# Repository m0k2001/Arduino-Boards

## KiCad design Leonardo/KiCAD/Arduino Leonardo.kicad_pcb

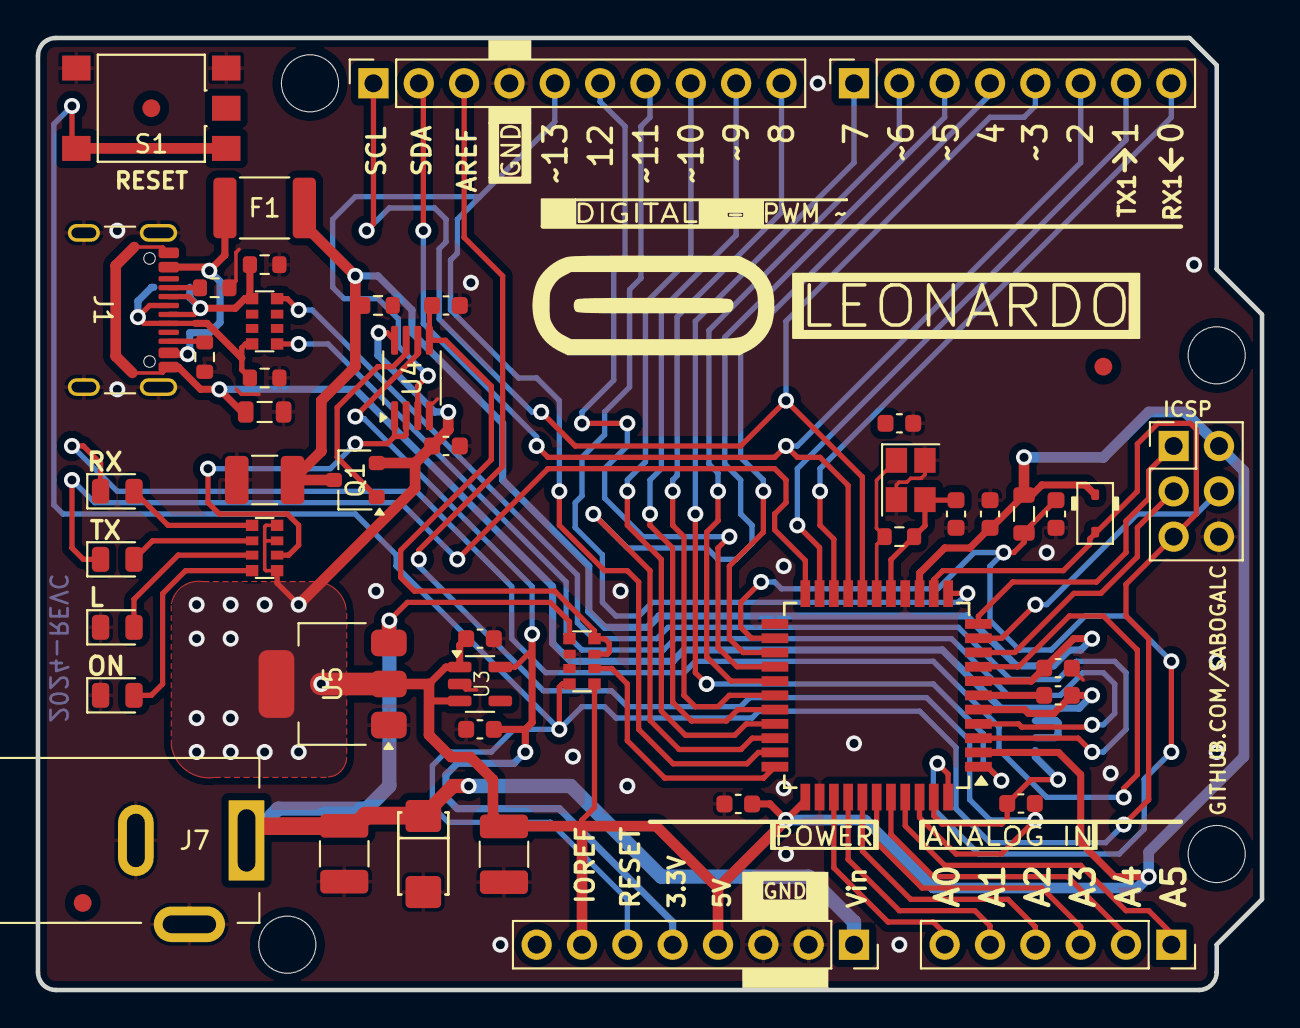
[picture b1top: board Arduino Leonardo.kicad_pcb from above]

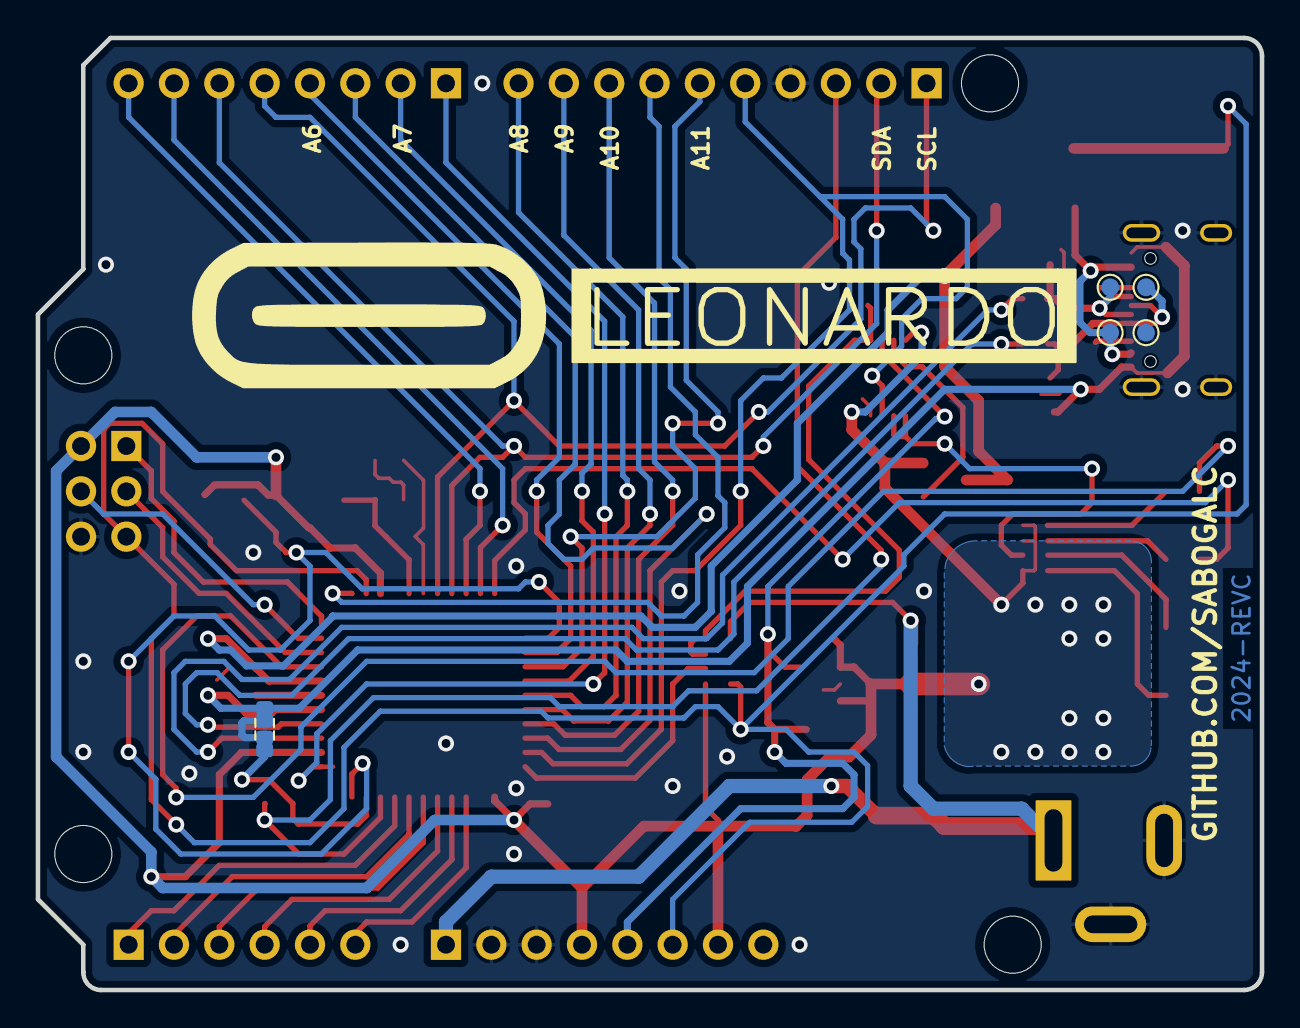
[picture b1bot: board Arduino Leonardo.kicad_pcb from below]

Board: 2 copper layers, 68.6 x 53.3 mm, 56 parts (6 on the bottom side), 53 nets.

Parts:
C1, C2, C6, C9, C13, C22: 100n; C_0603_1608Metric
C3, C4: 22p; C_0603_1608Metric
C5, C7, C11, C14: 1u; C_0603_1608Metric
C8, C10, C12: 10u; C_1210_3225Metric_Pad1.33x2.70mm_HandSolder
D1: M7; D_DO-214AC(SMA)
D2: 1N4148WS; D_SOD-323
D3, D5, D6: YELLOW; LED_0805_2012Metric
D4: GREEN; LED_0805_2012Metric
F1: MF-MSMF050-2; Fuse_1812_4532Metric_Pad1.30x3.40mm_HandSolder
FB1, FB2: 1kΩ@100MHz; L_0805_2012Metric
FID1, FID2, FID3: Fiducial; Fiducial_1mm_Mask2mm
J1: USB_C_Receptacle_USB2.0_16P; USB_C_Receptacle_GCT_USB4105-xx-A_16P_TopMnt_Horizontal
J2: PPTC101LFBN-RC; PinSocket_1x10_P2.54mm_Vertical
J3, J4: PPTC081LFBN-RC; PinSocket_1x08_P2.54mm_Vertical
J5: PPTC061LFBN-RC; PinSocket_1x06_P2.54mm_Vertical
J6: M20-9980345; PinHeader_2x03_P2.54mm_Vertical
J7: PJ-102AH; BarrelJack_Kycon_KLDX-0202-xC_Horizontal
Q1: FDN340P; SC-59
R1: 1M; R_0603_1608Metric
R2, R3: NM; R_0603_1608Metric
R4: 10k; R_0603_1608Metric
R5, R6: 5k1; R_0603_1608Metric
RN1: 10k; R_Array_Convex_4x0612
RN2: 1k; R_Array_Convex_4x0612
RN3: 22R; R_Array_Convex_4x0612
S1: TS06-667-30-BK-100-G-SMT-TR; SW_TS06-667-30-BK-100-G-SMT-TR
TP1, TP2, TP3, TP4: TestPoint; TestPoint_Pad_D1.0mm
U2: ATMEGA32U4-XU; TQFP-44_10x10mm_P0.8mm
U3: LP2985-3.3; SOT-23-5
U4: LMV358IDGKR; MSOP-8_3x3mm_P0.65mm
U5: NCP1117-5.0_SOT223; SOT-223-3_TabPin2
Y1: ECS-160-18-33-JGN-TR; Crystal_SMD_SeikoEpson_FA238-4Pin_3.2x2.5mm
Z1, Z2: 5pF@1MHz; R_0603_1608Metric

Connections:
+3.3V: C14.2, J4.5, U3.5 (VOUT), U4.6
+5V: C1.1, C2.1, C11.2, C12.1, C13.1, D2.1 (K), FB1.1, J4.4, J4.7, J6.2, Q1.2 (S), RN1.5 (R4.2), RN2.1 (R1.1), RN2.3 (R3.1), RN2.4 (R4.1), U2.2 (UVCC), U2.14 (VCC), U2.34 (VCC1), U3.1 (VIN), U3.3 (ON/~OFF), U4.8 (VCC+), U5.2 (VO)
A0: J5.6, U2.36 ((ADC7/TDI)PF7)
A1: J5.5, U2.37 ((ADC6/TDO)PF6)
A2: J5.4, U2.38 ((ADC5/TMS)PF5)
A3: J5.3, U2.39 ((ADC4/TCK)PF4)
A4: J5.2, U2.40 ((ADC1)PF1)
A5: J5.1, U2.41 ((ADC0)PF0)
AGND: C6.1, R2.1, U2.43 (GND3)
AREF: C6.2, J2.3, U2.42 (AREF)
AVCC: C5.1, FB1.2, U2.24 (AVCC), U2.44 (AVCC1)
CC1: J1.A5 (CC1), R5.1
CC2: J1.B5 (CC2), R6.1
CMP: C22.2, RN1.7 (R2.2), RN1.8 (R1.2), U4.5
D0/RX: J3.8, U2.20 ((RXD1/AIN1/INT2)PD2)
D1/TX: J3.7, U2.21 ((TXD1/INT3)PD3)
D2/SDA: J2.2, J3.6, U2.19 ((SDA/INT1)PD1)
D3/SCL: J2.1, J3.5, U2.18 ((OC0B/SCL/INT0)PD0)
D4: J3.4, U2.25 ((ICP1/ADC8)PD4)
D5*: J3.3, U2.31 ((OC3A/#0C4A)PC6)
D6*: J3.2, U2.27 ((T0/OC4D/ADC10)PD7)
D7: J3.1, U2.1 ((INT6/AIN0)PE6)
D+: J1.A6 (D+), J1.B6 (D+), RN3.8 (R1.2), TP3.1, Z1.1
D-: J1.A7 (D-), J1.B7 (D-), RN3.5 (R4.2), TP2.1, Z2.1
GATE_CMD: Q1.1 (G), U4.7
GND: C1.2, C2.2, C3.1, C4.2, C5.2, C8.2, C9.1, C10.2, C11.1, C12.2, C13.2, C14.1, C22.1, D1.2 (A), D3.1 (K), D4.1 (K), FB2.2, J1.S1 (SHIELD), J2.4, J4.2, J4.3, J6.6, J7.2, J7.3, R2.2, R3.1, R4.1, R5.2, R6.2, RN1.2 (R2.1), RN1.3 (R3.1), S1.3, S1.4, TP4.1, U2.15 (GND), U2.23 (GND1), U2.35 (GND2), U3.2 (GND), U4.4 (GND), U5.1 (GND), Y1.2, Y1.4, Z1.2, Z2.2
HWB: RN1.6 (R3.2), U2.33 ((#HWB)PE2)
IO8: J2.10, U2.28 ((ADC11/PCINT4)PB4)
IO9*: J2.9, U2.29 ((PCINT5/OC1A/#OC4B/ADC12)PB5)
IO10*: J2.8, U2.30 ((PCINT6/OC1B/OC4B/ADC13)PB6)
IO11*: J2.7, U2.12 ((PCINT7/OC0A/OC1C/#RTS)PB7)
IO12: J2.6, U2.26 ((T1/#OC4D/ADC9)PD6)
IO13*: J2.5, U2.32 ((ICP3/CLK0/OC4A)PC7), U4.3
LL: RN2.2 (R2.1), U4.1, U4.2
MISO: J6.1, U2.11 ((PD0/MISO/PCINT3)PB3)
MOSI: J6.4, U2.10 ((PDI/MOSI/PCINT2)PB2)
unnamed: D3.2 (A), RN2.7 (R2.2)
unnamed: D4.2 (A), RN2.8 (R1.2)
unnamed: D5.2 (A), RN2.6 (R3.2)
unnamed: D6.2 (A), RN2.5 (R4.2)
RD+: RN3.1 (R1.1), U2.4 (D+)
RD-: RN3.4 (R4.1), U2.3 (D-)
RESET: D2.2 (A), J4.6, J6.5, RN1.4 (R4.1), S1.1, S1.2, U2.13 (RESET)
RXLED: D6.1 (K), U2.8 ((SS/PCINT0)PB0)
SCK: J6.3, U2.9 ((SCLK/PCINT1)PB1)
TXLED: D5.1 (K), U2.22 ((XCK1/#CTS)PD5)
UCAP: C7.1, U2.6 (UCAP)
UGND: C7.2, FB2.1, J1.A1 (GND), J1.A12 (GND), J1.B1 (GND), J1.B12 (GND), R3.2, U2.5 (UGND)
VBUS: C8.1, C9.2, F1.1, Q1.3 (D), R4.2, U2.7 (VBUS)
VCC: C10.1, D1.1 (K), J4.1, J7.1, RN1.1 (R1.1), U5.3 (VI)
XTAL1: C4.1, R1.1, U2.17 (XTAL1), Y1.1
XTAL2: C3.2, R1.2, U2.16 (XTAL2), Y1.3
XUSB: F1.2, J1.A4 (VBUS), J1.A9 (VBUS), J1.B4 (VBUS), J1.B9 (VBUS), TP1.1

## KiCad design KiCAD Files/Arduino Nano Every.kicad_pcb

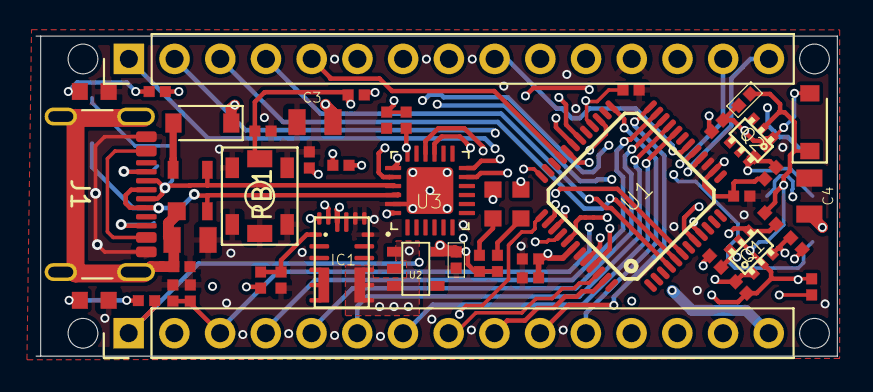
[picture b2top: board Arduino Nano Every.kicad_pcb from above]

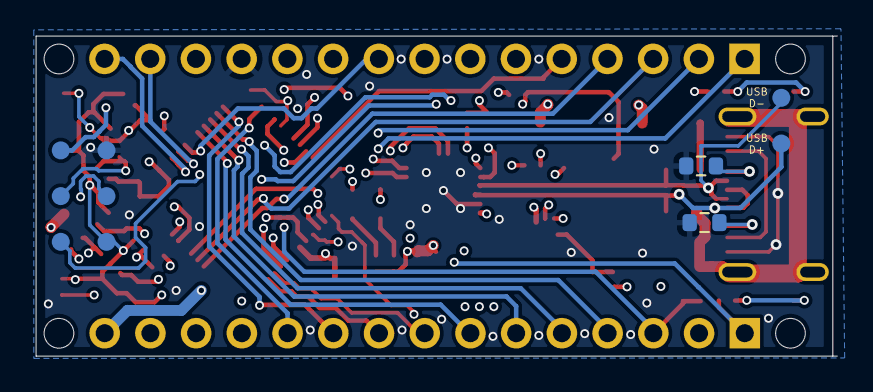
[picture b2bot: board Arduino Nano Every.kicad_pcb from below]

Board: 4 copper layers, 44.5 x 17.8 mm, 56 parts (2 on the bottom side), 31 nets.

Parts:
C1: 4n7; 0805-R2013X50N
C2, C7, C7#2, C8, C10, C11: 100n; 0402-1005X55N
C3, C4: 22u; 0805-R2013X50N
C5, C9: 4u7; 0402-1005X55N
C6: 1u; 0402-1005X55N
D1: PRTR5V; SOT190P230X110-4N
D2: PMEG6020; SODFL3517X110N
D3: DNP; SODFL3517X110N
D+0: DNP; TP-1.00MM
D-0: DNP; TP-1.00MM
DL1, DL3, DL4: YELLOW; LEDC1608X80N-AK
DL2: GREEN; LEDC1608X80N-AK
IC1: MPM3610
J1: USB_C_Receptacle_USB2.0_16P; USB_C_Receptacle_GCT_USB4105-xx-A_16P_TopMnt_Horizontal
J2: DNP; 2X03-TP
PB1: PTS820; C&K_PTS820_NO_HOLES
Q1, Q2: BSS138PS; SOT363
R1: 1M; 0402-1005X55N
R1#2, R1#3: 5K1; R_0603_1608Metric
R2, R3, R12, R13: 330R; 0402-1005X55N
R4, R6, R10: 100k; 0402-1005X55N
R5, R11, R14, R15, R16, R17, R18, R19: 4k7; 0402-1005X55N
R7: 0R; 0402-1005X55N
R8: 19k1; 0402-1005X55N
R9: 39k; 0402-1005X55N
R20: DNP; 0402-1005X55N
U1: ATMEGA4809; TQFP48
U2: AP2112K-3.3; SOT25
U3: ATSAMD11D14A; HVQFN24
UNK_HOLE_0: dummyfp0
UNK_HOLE_1: dummyfp1
UNK_HOLE_2: dummyfp2
UNK_HOLE_3: dummyfp3

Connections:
$NS1: C1.1, D1.1, R1.2
+3V3: C6.1, C11.2, D3.C, J2.1, Q1.2 (G), Q1.5 (G), Q2.2 (G), R2.2, R5.2, R11.1, R12.2, R13.2, R14.2, R16.2, R18.2, U2.5 (OUT), U3.24 (VDDIO@1)
+5V: C3.1, C7#2.1, C8.2, C9.2, C10.2, D2.C, IC1.7 (OUT), IC1.8 (OUT), IC1.9 (OUT), IC1.20 (OUT), R4.2, R6.2, R15.2, R17.2, R19.2, U1.14 (VDD@2), U1.28 (AVDD), U1.42 (VDD@1), U2.1 (IN), U2.3 (EN)
/A4/SDA: U1.36 (PF02), U1.46 (PA02)
/A5/SCL: U1.37 (PF03), U1.47 (PA03)
/AREF: C5.1, C7.1, U1.27 (PD07)
/RESETN: C2.1, PB1.6 (2), R4.1, U1.40 (RST/PF06)
/RX0: Q1.6 (D), R17.1, U1.9 (PB05)
/RX_D11: DL3.C, Q1.4 (S), R14.1, U3.16 (PA23)
/RX_UPDI: R7.2, U3.12 (PA15)
/SCK: R3.2, U1.32 (PE02)
/TX0: Q1.3 (D), R15.1, U1.8 (PB04)
/TX_D11: DL4.C, Q1.1 (S), R16.1, U3.15 (PA22)
/TX_UPDI: D3.A, Q2.1 (S), R7.1, R18.1, R20.1, U3.11 (PA14)
/UPDI: J2.4, Q2.6 (D), R19.1, R20.2, U1.41 (UPDI)
/USB_N: D1.3, D-0.X, J1.A7 (D-), J1.B7 (D-), U3.21 (PA24/USB_DM)
/USB_P: D1.2, D+0.X, J1.A6 (D+), J1.B6 (D+), U3.22 (PA25/USB_DP)
GND: C1.2, C2.2, C3.2, C4.2, C5.2, C6.2, C7.2, C7#2.2, C8.1, C9.1, C10.1, C11.1, DL1.C, DL2.C, IC1.3 (AGND), IC1.12 (GND), IC1.13 (GND), IC1.14 (GND), J1.A1 (GND), J1.A12 (GND), J1.B1 (GND), J1.B12 (GND), J2.5, PB1.1 (3), PB1.2 (3), PB1.3, PB1.4 (3), PB1.5 (1), R1.1, R1#2.1, R1#3.1, R8.1, R9.1, U1.15 (GND@3), U1.29 (GND@2), U1.43 (GND@1), U2.2 (GND/ADJ), U3.23 (GND@1), U3.EXP (EP)
unnamed: DL1.A, R3.1
unnamed: DL2.A, R2.1
unnamed: DL3.A, R12.1
unnamed: DL4.A, R13.1
unnamed: IC1.18 (AAM), R9.2
unnamed: IC1.17 (EN), R10.1
unnamed: IC1.1 (FB), R6.1, R8.2
unnamed: IC1.4 (SW), IC1.5 (SW), IC1.6 (SW), IC1.19 (SW)
unnamed: J2.6, R5.1, U3.18 (PA28/RESETN)
unnamed: J2.3, R11.2, U3.19 (PA30/SWCLK)
unnamed: J2.2, U3.20 (PA31/SWDIO)
VIN: C4.1, IC1.16 (VIN), R10.2
VUSB: D1.4, D2.A, J1.A4 (VBUS), J1.A9 (VBUS), J1.B4 (VBUS), J1.B9 (VBUS)

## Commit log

2026-04-01 Directory modified
2026-04-01 Add Leonardo USB C
